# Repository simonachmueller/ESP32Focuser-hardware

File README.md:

# ESP32Focuser Hardware
This is a repository for storing documentation for my [ESP32Focuser](https://github.com/simonachmueller/ESP32Focuser) project.

Описание 

Deutsche 

# What is that about
Focuser for astronomy telescope based on ESP32 controller. Comportable with Indilib (http:/indilib.org/) and ASCOM (https://ascom-standards.org/).
The controller uses the protocol Moonlite (as documented in the indilib project).

# What hardware do I need
The firmware runs on a [ESP32-DevKitC](https://www.espressif.com/en/products/devkits/esp32-devkitc/overview) board. It uses also the [BIGTREETECH TMC2209 V1.2 Stepper Motor Driver](https://github.com/bigtreetech/BIGTREETECH-TMC2209-V1.2) to drive the motor on a super-silent and vibrationless way. Basically, you only need this two boards to start using the focuser. If you want to build it on a more resilient way, you can follow intructions below.

# Schematics
Schematics diagram can be found as a KiCad project [folder](/schematics). You can donwload shematics as pdf [here](/schematics/ESP32Focuser.sch.pdf).

The schematics is pretty easy. You just connect the pins of the ESP32 dev board with the TMC2209 board, add power supply and connect motor - from this point you can control the focuser from the computer over ASCOM/INDI driver. If you want to use an optical encoder as a handcontroller (what I would really advise you if you want to get rid of vibrations when you touch the telescope focuser knob), connect it to the pins on the ESP32 board as well.

## Wiring table
Please use the wiring table as reference, it might get outdated. For the most latest schematics version, check the KiCad project.

| Description | ESP32 board | TMC2209 board | Note |
| ----------- | ----------- | ------------- | ---- | 
| DIR         | 32          | DIR           |      |
| STEP        | 33          | STEP          |      |
| CLK         | 25          | CLK           |      |
| PDN         | 26          | PDN + PDN     | not used |
| MS2         | 14          | MS2           |      |
| MS1         | 12          | MS1           |      |
| EN          | 13          | EN            |      |
| ENC1        | 2           |               | Encoder output 1 |
| ENC2        | 15          |               | Encoder output 2 |
| 5V          | 5V          | VDD           |      |
| 12V         |             | VM            | Motor power supply |

## Stepper motor
I use the 17HS2408 stepper motor, as it fits well for 12v supply: it has 8 Ohm phase resistance what leads to 1.5 Amps phase current, it's a bit over the specification (rated current 0.6 Amps) but as it's not supposed to continuously work on high speed in this project,it works just fine, has enough torque and does smooth movements. 

## BOM
Aka bill of material

|     Description           |                   AliExpress link                    |  Notes          |
| ------------------------- | ---------------------------------------------------- | --------------- | 
| ESP32-DevKitC             | https://www.aliexpress.com/item/4000103411061.html   |  |
| 17HS2408 stepper motor    | https://www.aliexpress.com/item/33033986185.html     |  |
| 7 M3 screws for motor and encoder  | https://www.aliexpress.com/item/32965979997.html     | M3 50pcs + 5mm  |
| TMC2209 board             | https://www.aliexpress.com/item/33029587820.html     |  |
| Optical rotary encoder CALT ES38    | https://www.aliexpress.com/item/33028641351.html | 5v 600ppr  |
| 13x32mm Encoder knob | https://www.aliexpress.com/item/33039964137.html | |
| Motor shaft coupler 5mm x ?? mm| https://www.aliexpress.com/item/32913158582.html ||
| OR alternatively to the direct coupling your motor with the focuser, you could use a belt like this below|||
| GT2 Pulley 20 tooth ø 5mm| https://www.aliexpress.com/item/32724156349.html ||
| GT2 Closed Loop Timing Belt | https://www.aliexpress.com/item/32950422029.html ||
| 12v female plug 5.5mm x 2.1mm | |  |
| 12v→5v DC-DC step down converter board| https://www.aliexpress.com/item/32742116421.html ||
| Hand controller connector M GX12 5 pin for encoder | https://www.aliexpress.com/item/32869491577.html | |
| Hand controller connector M GX12 4 pin for motor | https://www.aliexpress.com/item/32869491577.html | |
| 115 90 55mm plastic enclosure case | https://www.aliexpress.com/item/32709832386.html |  |
| 100x68x50mm plastic enclosure case for encoder | https://www.aliexpress.com/item/32792270384.html | |
| Push button for handcontroller | https://www.aliexpress.com/item/32965284265.html ||
| Micro USB cable | tbd | |
| 2.54mm Wire Cable Connector 4 pin | https://www.aliexpress.com/item/32954418743.html | |
| Prototyping board 5x7 cm | https://www.aliexpress.com/item/32853911495.html |  |
| Cable for motor 4 cores 0.3mm 22awg | https://www.aliexpress.com/item/4000714461664.html | |

# Pictures

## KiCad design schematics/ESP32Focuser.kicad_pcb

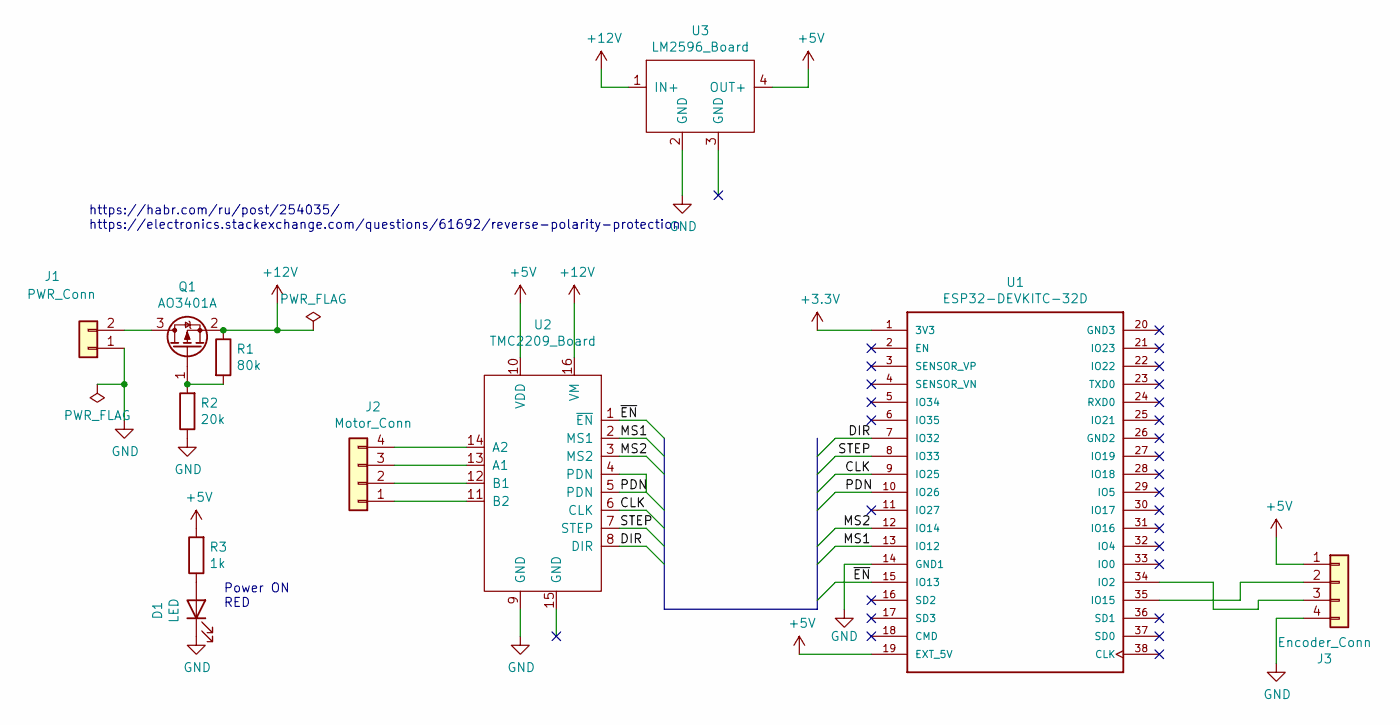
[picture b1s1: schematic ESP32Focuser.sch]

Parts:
D1: LED; LED_D3.0mm
J1: PWR_Conn; PinSocket_1x02_P2.54mm_Vertical
J2: Motor_Conn; PinSocket_1x04_P2.54mm_Vertical
J3: Encoder_Conn; PinSocket_1x04_P2.54mm_Vertical
Q1: AO3401A; SOT-23
R1: 80k; R_0805_2012Metric_Pad1.15x1.40mm_HandSolder
R2: 20k; R_0805_2012Metric_Pad1.15x1.40mm_HandSolder
R3: 1k; R_0805_2012Metric_Pad1.15x1.40mm_HandSolder
U1: ESP32-DEVKITC-32D; MODULE_ESP32-DEVKITC-32D
U2: TMC2209_Board; TMC2209_Module
U3: LM2596_Board; LM2596_Module

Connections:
+3V3: U1.1 (3V3)
+5V: J3.1, R3.2, U1.19 (EXT_5V), U2.10 (VDD), U3.4 (OUT+)
+12V: Q1.2 (S), R1.1, U2.16 (VM), U3.1 (IN+)
/CLK: U1.9 (IO25), U2.6 (CLK)
/DIR: U1.7 (IO32), U2.8 (DIR)
/MS1: U1.13 (IO12), U2.2 (MS1)
/MS2: U1.12 (IO14), U2.3 (MS2)
/PDN: U1.10 (IO26), U2.4 (PDN), U2.5 (PDN)
/STEP: U1.8 (IO33), U2.7 (STEP)
/~EN: U1.15 (IO13), U2.1 (~EN)
GND: D1.1 (K), J1.1, J3.4, R2.1, U1.14 (GND1), U2.9 (GND), U3.2 (GND)
unnamed: D1.2 (A), R3.1
unnamed: J1.2, Q1.3 (D)
unnamed: J2.1, U2.11 (B2)
unnamed: J2.2, U2.12 (B1)
unnamed: J2.3, U2.13 (A1)
unnamed: J2.4, U2.14 (A2)
unnamed: J3.2, U1.35 (IO15)
unnamed: J3.3, U1.34 (IO2)
unnamed: Q1.1 (G), R1.2, R2.2

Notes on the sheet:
https://habr.com/ru/post/254035/ https://electronics.stackexchange.com/questions/61692/reverse-polarity-protection
Power ON RED

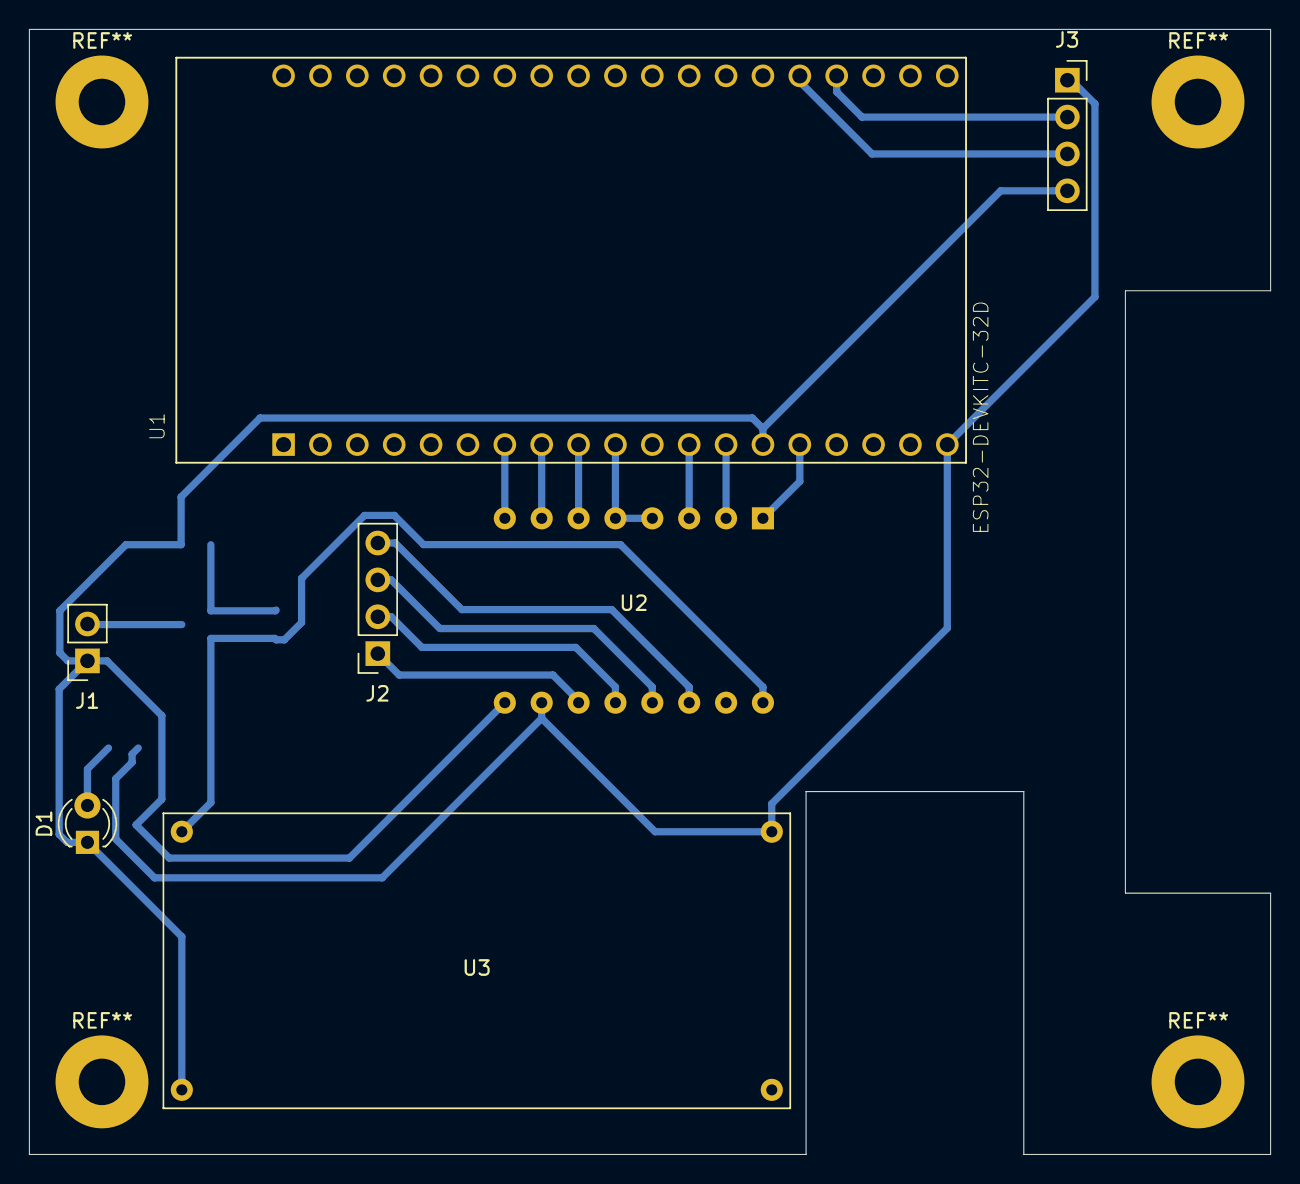
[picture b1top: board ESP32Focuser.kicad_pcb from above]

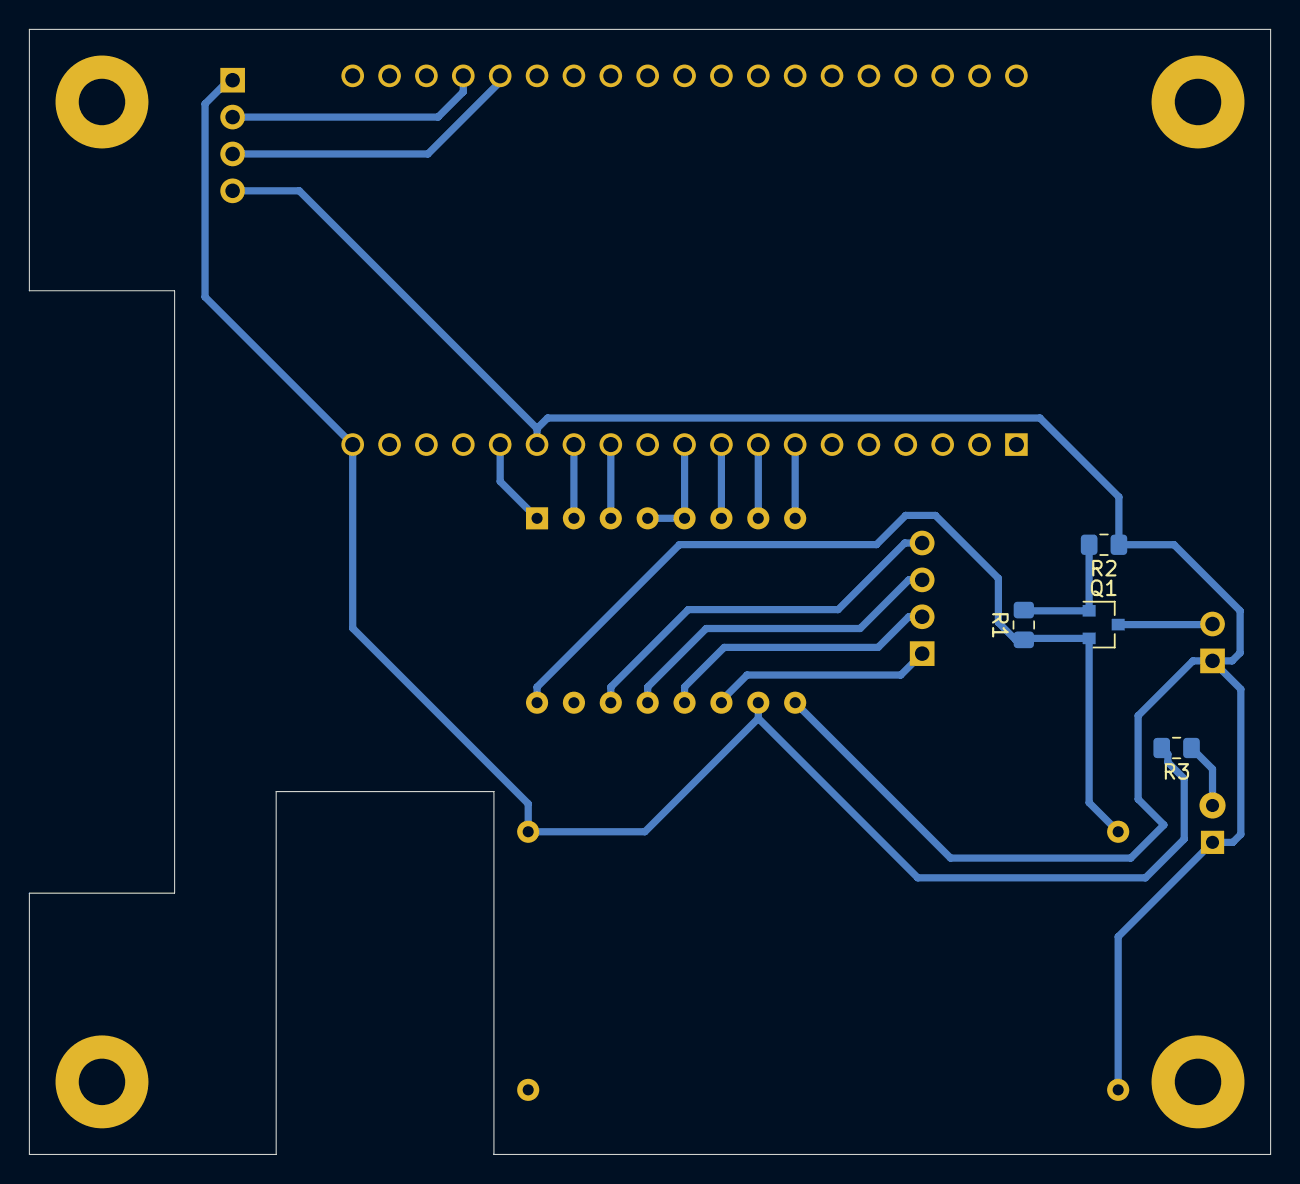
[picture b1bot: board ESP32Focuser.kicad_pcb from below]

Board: 2 copper layers, 85.5 x 77.5 mm, 11 parts (4 on the bottom side), 19 nets.

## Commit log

2020-11-16 Initial commit, KiCad project, pictures
2020-11-16 Add motor information
2020-11-16 fix typo
2020-11-17 Add bill of material
2020-11-17 Fix pictures
2020-11-17 Fix images again
2020-11-17 Add more pictures and links
2020-11-17 Add stepper motor picture
2020-11-17 Fix http links
2020-11-17 Add optical encoder
2020-11-17 Add prototyping board and wire connector
2020-11-17 Add motor cable
2020-11-28 Add information about the timing belt option
2020-12-05 add another picture
2020-12-06 Add schematics as pdf
2020-12-06 Add link to schematics
2021-01-09 Add new installation pictures
2021-01-09 Add russion description
2021-01-09 Fix links
2021-01-09 Fix formatting
2021-01-09 Add German readme
2021-01-09 Fix wording
